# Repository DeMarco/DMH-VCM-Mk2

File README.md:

# DMH-VCM-Mk2
Better iteration of the Tripple VCA, this time with smaller offset knobs to make space for CV amount attenuverters.

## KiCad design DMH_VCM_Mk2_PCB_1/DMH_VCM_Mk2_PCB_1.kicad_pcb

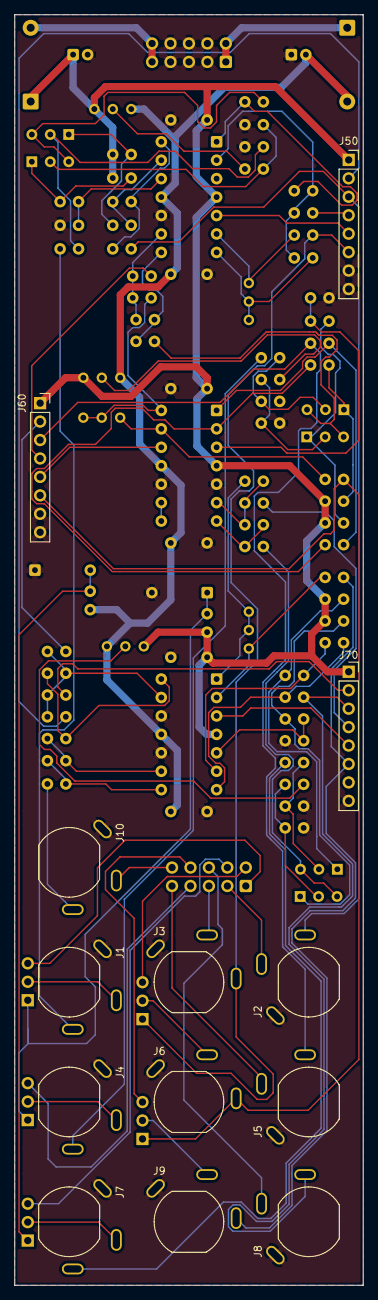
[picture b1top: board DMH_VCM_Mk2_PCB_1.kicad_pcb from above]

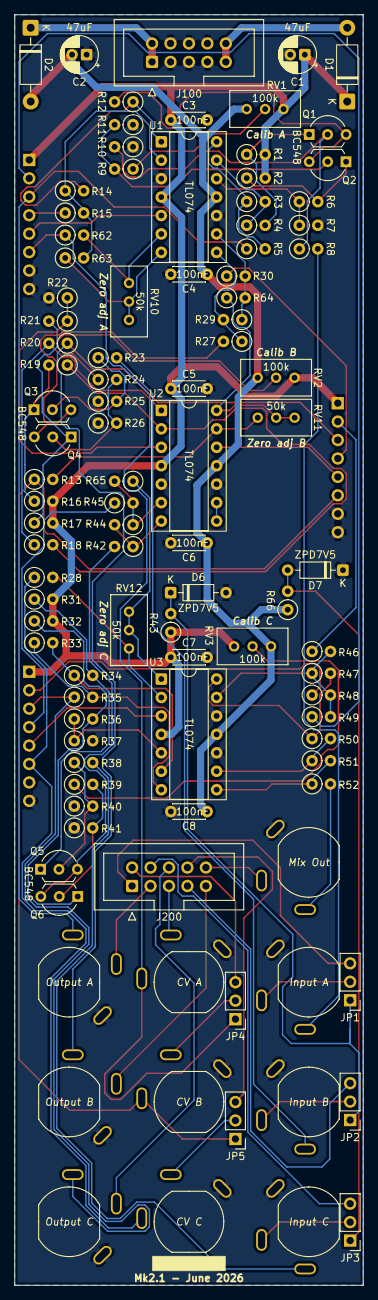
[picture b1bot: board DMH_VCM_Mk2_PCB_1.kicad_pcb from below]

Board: 2 copper layers, 48.0 x 175.0 mm, 104 parts (91 on the bottom side), 85 nets.

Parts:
C1, C2: 47uF; CP_Radial_D5.0mm_P2.00mm
C3, C4, C5, C6, C7, C8: 100nF; C_Disc_D4.3mm_W1.9mm_P5.00mm
D1, D2: SB140; D_DO-41_SOD81_P10.16mm_Horizontal
D6, D7: ZPD7V5; D_DO-35_SOD27_P7.62mm_Horizontal
J1, J2, J3, J4, J5, J6, J7, J8, J9, J10: TS_Jack_6.35mm_Sw; CUI_MJ-63052A
J50, J60, J70: Conn_01x08; PinSocket_1x08_P2.54mm_Vertical
J100: IDC_02x05; IDC-Header_2x05_P2.54mm_Vertical_Eurorack
J200: IDC_02x05; IDC-Header_2x05_P2.54mm_Vertical_BackBone
JP1, JP2, JP3, JP4, JP5: Jumper_3_Bridged12; PinHeader_1x03_P2.54mm_Vertical
Q1, Q2, Q3, Q4, Q5, Q6: BC548; TO-92L_Inline_Wide
R1, R2, R16, R17, R31, R32: 20k; R_Axial_DIN0207_L6.3mm_D2.5mm_P2.54mm_Vertical
R3, R7, R8, R9, R14, R15, R18, R22, R23, R24, R29, R30, R33, R37, R38, R39, R44, R45, R46, R47, R48, R49, R50, R51, R63, R64, R65: 100k; R_Axial_DIN0207_L6.3mm_D2.5mm_P2.54mm_Vertical
R4, R6, R12, R19, R21, R27, R34, R36, R42: 10k; R_Axial_DIN0207_L6.3mm_D2.5mm_P2.54mm_Vertical
R5, R20, R35, R43, R52, R66: 1k; R_Axial_DIN0207_L6.3mm_D2.5mm_P2.54mm_Vertical
R10, R11, R25, R26, R40, R41: 100R; R_Axial_DIN0207_L6.3mm_D2.5mm_P2.54mm_Vertical
R13, R28, R62: 33k; R_Axial_DIN0207_L6.3mm_D2.5mm_P2.54mm_Vertical
RV1, RV2, RV3: 100k; Potentiometer_Bourns_3296W_Vertical
RV10, RV11, RV12: 50k; Potentiometer_Bourns_3296W_Vertical
U1, U2, U3: TL074; DIP-14_W7.62mm_Socket

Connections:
+12V: C1.1, C3.1, C5.1, C7.1, D1.1 (K), J50.1, J60.1, J70.1, R1.2, R2.2, R16.2, R17.2, R31.2, R32.2, R43.1, RV1.3, RV2.3, RV3.3, U1.4 (V+), U2.4 (V+), U3.4 (V+)
-12V: C2.2, C4.2, C6.2, C8.2, D2.2 (A), R66.1, RV1.1, RV2.1, RV3.1, U1.11 (V-), U2.11 (V-), U3.11 (V-)
/Inputs and Outputs/CV A Jack: J3.T, J50.6, JP4.1 (A), R62.1
/Inputs and Outputs/CV Amt A Pot: J50.5, U1.5 (+)
/Inputs and Outputs/CV Amt B Pot: J60.5, U2.12 (+)
/Inputs and Outputs/CV Amt C Pot: J70.5, U3.3 (+)
/Inputs and Outputs/CV B Jack: J6.T, J60.6, JP5.1 (A), R13.1
/Inputs and Outputs/CV C Jack: J9.T, J70.6, R28.1
/Inputs and Outputs/Input A Jack: J1.T, R8.2
/Inputs and Outputs/Input B Jack: J4.T, R23.2
/Inputs and Outputs/Input C Jack: J7.T, R38.2
/Inputs and Outputs/Mix Out Jack: J10.T, R52.2
/Inputs and Outputs/Mute A Switch: J50.2, R49.1
/Inputs and Outputs/Mute B Switch: J60.2, R46.1
/Inputs and Outputs/Mute C Switch: J70.2, R48.1
/Inputs and Outputs/Offset A Pot: J50.4, R15.1
/Inputs and Outputs/Offset B Pot: J60.4, R30.1
/Inputs and Outputs/Offset C Pot: J70.4, R45.1
/Inputs and Outputs/Output A Jack: J2.T, J50.3, R5.1
/Inputs and Outputs/Output B Jack: J5.T, J60.3, R20.1
/Inputs and Outputs/Output C Jack: J8.T, J70.3, R35.1
GND: C1.2, C2.1, C3.2, C4.1, C5.2, C6.1, C7.2, C8.1, D6.2 (A), D7.1 (K), J1.S, J2.S, J3.S, J4.S, J5.S, J6.S, J7.S, J8.S, J9.S, J10.S, J50.7, J50.8, J60.7, J60.8, J70.8, J100.2a, J100.2b, J100.3a, J100.3b, J100.4a, J100.4b, R7.2, R10.1, R11.1, R22.2, R25.1, R26.1, R37.2, R40.1, R41.1, U1.3 (+), U1.10 (+), U2.5 (+), U2.10 (+), U3.10 (+), U3.12 (+)
unnamed: D1.2 (A), J100.5a, J100.5b
unnamed: D2.1 (K), J100.1a, J100.1b
unnamed: D6.1 (K), JP1.1 (A), JP2.1 (A), R43.2
unnamed: D7.2 (A), JP3.1 (A), R66.2
unnamed: J200.1, JP1.3 (B)
unnamed: J2.TN, J200.2
unnamed: J3.TN, J200.3
unnamed: J200.4, JP2.3 (B)
unnamed: J5.TN, J200.5
unnamed: J200.6, JP4.3 (B)
unnamed: J200.7, JP3.3 (B)
unnamed: J8.TN, J200.8
unnamed: J200.9, JP5.3 (B)
unnamed: J10.TN, J200.10
unnamed: J1.TN, JP1.2 (C)
unnamed: J4.TN, JP2.2 (C)
unnamed: J7.TN, JP3.2 (C)
unnamed: J6.TN, JP4.2 (C)
unnamed: J9.TN, JP5.2 (C)
unnamed: Q1.2 (B), R8.1, R10.2
unnamed: Q1.1 (C), R1.1, R4.2
unnamed: Q1.3 (E), Q2.3 (E), R12.2
unnamed: Q2.2 (B), R9.2, R11.2
unnamed: Q2.1 (C), R2.1, R6.2
unnamed: Q3.2 (B), R23.1, R25.2
unnamed: Q3.1 (C), R16.1, R19.2
unnamed: Q3.3 (E), Q4.3 (E), R27.2
unnamed: Q4.2 (B), R24.2, R26.2
unnamed: Q4.1 (C), R17.1, R21.2
unnamed: Q5.2 (B), R38.1, R40.2
unnamed: Q5.1 (C), R31.1, R34.2
unnamed: Q5.3 (E), Q6.3 (E), R42.2
unnamed: Q6.2 (B), R39.2, R41.2
unnamed: Q6.1 (C), R32.1, R36.2
unnamed: R3.1, R5.2, U1.14
unnamed: R9.1, RV1.2
unnamed: R12.1, R14.2, U1.1
unnamed: R18.1, R20.2, U2.1
unnamed: R24.1, RV2.2
unnamed: R27.1, R29.2, U1.8
unnamed: R33.1, R35.2, U3.7
unnamed: R39.1, RV3.2
unnamed: R42.1, R44.2, U2.7
unnamed: R47.2, R50.1, U3.14
unnamed: R51.2, R52.1, U3.8
unnamed: R63.1, RV10.2, RV10.3, U1.7
unnamed: R64.1, RV11.2, RV11.3, U2.14
unnamed: R65.1, RV12.2, RV12.3, U3.1
unnamed: R14.1, R15.2, R63.2, U1.2 (-)
unnamed: R62.2, RV10.1, U1.6 (-)
unnamed: R29.1, R30.2, R64.2, U1.9 (-)
unnamed: R6.1, R7.1, U1.12 (+)
unnamed: R3.2, R4.1, U1.13 (-)
unnamed: R21.1, R22.1, U2.3 (+)
unnamed: R18.2, R19.1, U2.2 (-)
unnamed: R44.1, R45.2, R65.2, U2.6 (-)
unnamed: U2.8, U2.9 (-)
unnamed: R13.2, RV11.1, U2.13 (-)
unnamed: R28.2, RV12.1, U3.2 (-)
unnamed: R36.1, R37.1, U3.5 (+)
unnamed: R33.2, R34.1, U3.6 (-)
unnamed: R50.2, R51.1, U3.9 (-)
unnamed: R46.2, R47.1, R48.2, R49.2, U3.13 (-)

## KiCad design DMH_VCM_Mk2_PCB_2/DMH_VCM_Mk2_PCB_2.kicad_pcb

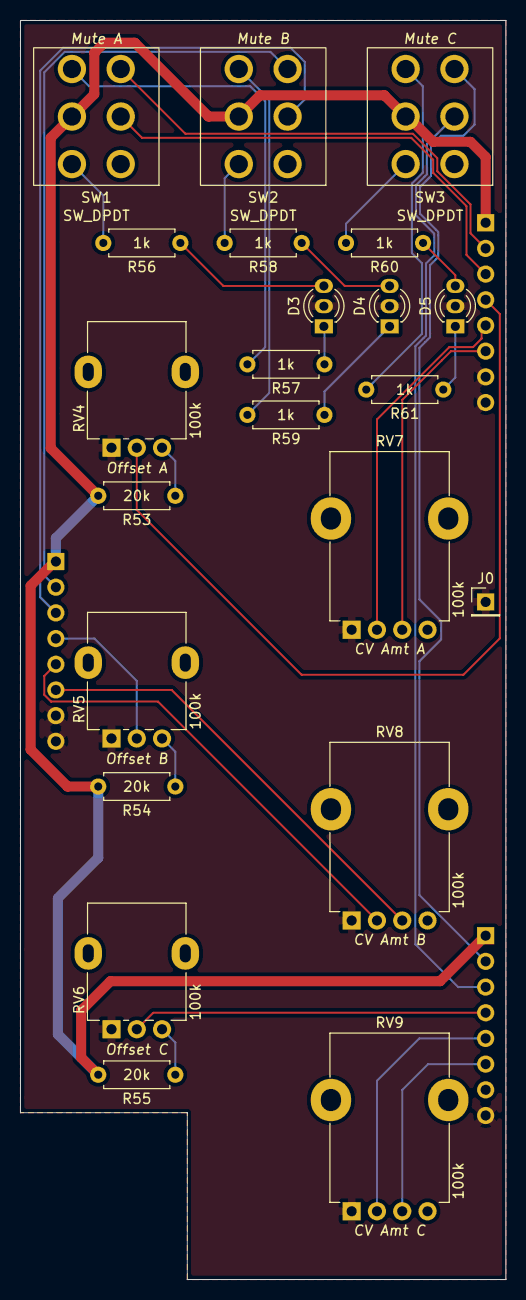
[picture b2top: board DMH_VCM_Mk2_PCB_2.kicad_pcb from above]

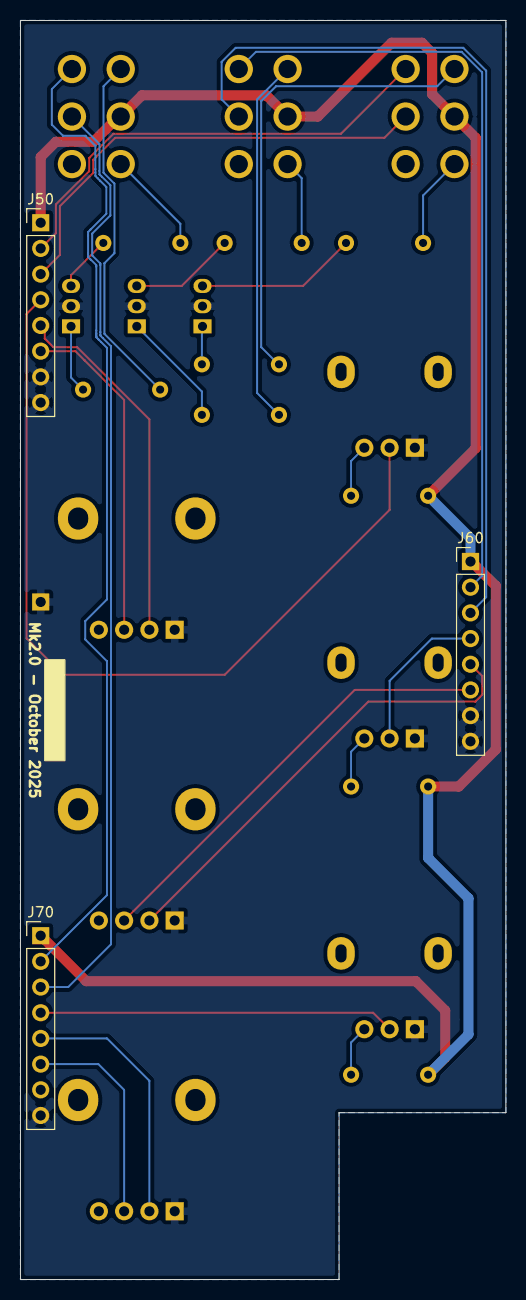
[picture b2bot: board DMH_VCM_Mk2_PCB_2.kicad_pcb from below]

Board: 2 copper layers, 48.0 x 124.5 mm, 25 parts (3 on the bottom side), 32 nets.

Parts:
D3, D4, D5: LED_Dual_AKA; LED_D3.0mm-2color
J0: Conn_01x01; PinHeader_1x01_P2.54mm_Vertical
J50, J60, J70: Conn_01x08; PinHeader_1x08_P2.54mm_Vertical
R53, R54, R55: 20k; R_Axial_DIN0207_L6.3mm_D2.5mm_P7.62mm_Horizontal
R56, R57, R58, R59, R60, R61: 1k; R_Axial_DIN0207_L6.3mm_D2.5mm_P7.62mm_Horizontal
RV4, RV5, RV6: 100k; Potentiometer_Alpha_RD901F-40-00D_Single_Vertical
RV7, RV8, RV9: 100k; Potentiometer_TT_P110KH1
SW1, SW2, SW3: SW_DPDT; Toggle_Switch_2_Poles_TE

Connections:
+12V: J50.1, J60.1, J70.1, R53.2, R54.2, R55.2, SW1.5 (B), SW2.5 (B), SW3.5 (B)
/Inputs and Outputs/CV A Jack: J50.6, RV7.3
/Inputs and Outputs/CV Amt A Pot: J50.5, RV7.2
/Inputs and Outputs/CV Amt B Pot: J60.5, RV8.2
/Inputs and Outputs/CV Amt C Pot: J70.5, RV9.2
/Inputs and Outputs/CV B Jack: J60.6, RV8.3
/Inputs and Outputs/CV C Jack: J70.6, RV9.3
/Inputs and Outputs/Mute A Switch: J50.2, SW1.1 (A)
/Inputs and Outputs/Mute B Switch: J60.2, SW2.1 (A)
/Inputs and Outputs/Mute C Switch: J70.2, SW3.1 (A)
/Inputs and Outputs/Offset A Pot: J50.4, RV4.2
/Inputs and Outputs/Offset B Pot: J60.4, RV5.2
/Inputs and Outputs/Offset C Pot: J70.4, RV6.2
/Inputs and Outputs/Output A Jack: J50.3, SW1.2 (B)
/Inputs and Outputs/Output B Jack: J60.3, SW2.2 (B)
/Inputs and Outputs/Output C Jack: J70.3, SW3.2 (B)
GND: D3.2 (K), D4.2 (K), D5.2 (K), J0.1 (Pin_1_1), J50.7, J50.8, J60.7, J60.8, J70.8, RV4.1, RV5.1, RV6.1, RV7.1, RV8.1, RV9.1
unnamed: D3.1 (A1), R57.1
unnamed: D3.3 (A2), R56.1
unnamed: D4.1 (A1), R59.1
unnamed: D4.3 (A2), R58.1
unnamed: D5.1 (A1), R61.1
unnamed: D5.3 (A2), R60.1
unnamed: R53.1, RV4.3
unnamed: R54.1, RV5.3
unnamed: R55.1, RV6.3
unnamed: R56.2, SW1.6 (C)
unnamed: R57.2, SW1.4 (A)
unnamed: R58.2, SW2.6 (C)
unnamed: R59.2, SW2.4 (A)
unnamed: R60.2, SW3.6 (C)
unnamed: R61.2, SW3.4 (A)

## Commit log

2025-04-25 Created Panel project
2025-04-25 Updated symbols and fps as per library
2025-06-16 Added PCB 1 project
2025-06-16 Almost finished PCB 1 schematic
2025-06-20 PCB 1 placement in progress
2025-06-21 PCB 1 placement done
2025-06-21 PCB 1 routine in progress
2025-06-21 PCB 1 routing still in progress
2025-06-21 Completed PCB 1 routing
2025-06-21 Fixed routing bugs
2025-06-21 Optimized PCB 1 routing
2025-06-22 Created PCB 2 project
2025-06-22 Positioned PCB 2 components
    Volume conflict with headers, needs correction o PCB 1
2025-06-25 Resolved J50 volume conflict
    J70 still to be solved
2025-06-25 Resolved J70 volume conflict
2025-06-26 Finished routing PCB 2
2025-10-04 Generated Gerbers
2025-10-13 Added resistor values to PCB
2026-06-13 Kicad 10 and updated SynthStuff
2026-06-20 Added +/-7v5 to input TN and normalled CV inputs
